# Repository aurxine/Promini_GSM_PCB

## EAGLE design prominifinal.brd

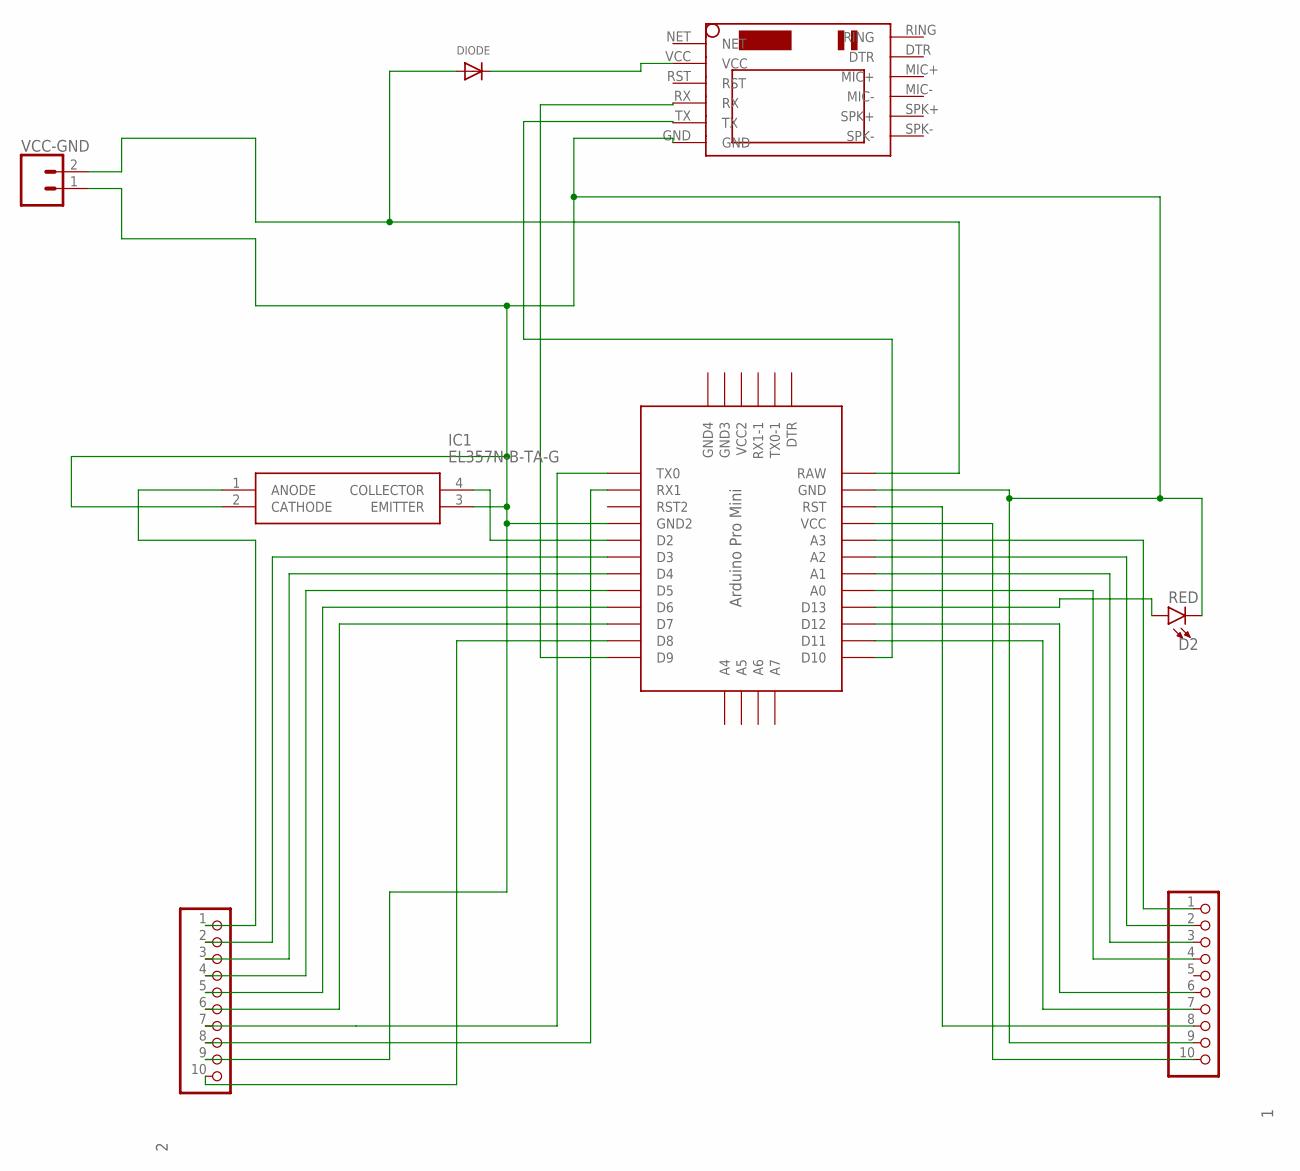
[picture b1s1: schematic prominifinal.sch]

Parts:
1, 2: PINHD-1X10; 1X10
D2: RED; LED-1206
DIODE: DIODESOD-323F; SOD-323F
IC1: EL357N-B-TA-G; SOP254P700X200-4N
PROMINI: PRO-MINI
U$1: SIM800LMODULE
VCC-GND: CONN_025MM; SCREWTERMINAL-5MM-2

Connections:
D2,D3,D4,D5-IO0,D6-IO2,D7-IO4,D8-IO5,D9-IO9,GND,VIN: 2.6, PROMINI.D7
unnamed: DIODE.A, PROMINI.RAW, VCC-GND.2
unnamed: 2.8, PROMINI.RX1
unnamed: DIODE.C, U$1.VCC
unnamed: 1.10, PROMINI.VCC
unnamed: IC1.4 (COLLECTOR), PROMINI.D2
unnamed: PROMINI.D9, U$1.RX
unnamed: D2.A, PROMINI.D13
unnamed: 2.1, IC1.1 (ANODE)
unnamed: 2.2, PROMINI.D3
unnamed: 2.3, PROMINI.D4
unnamed: 2.4, PROMINI.D5
unnamed: 2.5, PROMINI.D6
unnamed: 1.8, PROMINI.RST
unnamed: 2.7, PROMINI.TX0
unnamed: 2.10, PROMINI.D8
unnamed: 1.1, PROMINI.A3
unnamed: 1.2, PROMINI.A2
unnamed: 1.3, PROMINI.A1
unnamed: 1.4, PROMINI.A0
unnamed: 1.6, PROMINI.D12
unnamed: 1.7, PROMINI.D11
unnamed: PROMINI.D10, U$1.TX
unnamed: 1.9, 2.9, D2.C, IC1.2 (CATHODE), IC1.3 (EMITTER), PROMINI.GND, PROMINI.GND1 (GND2), U$1.GND, VCC-GND.1

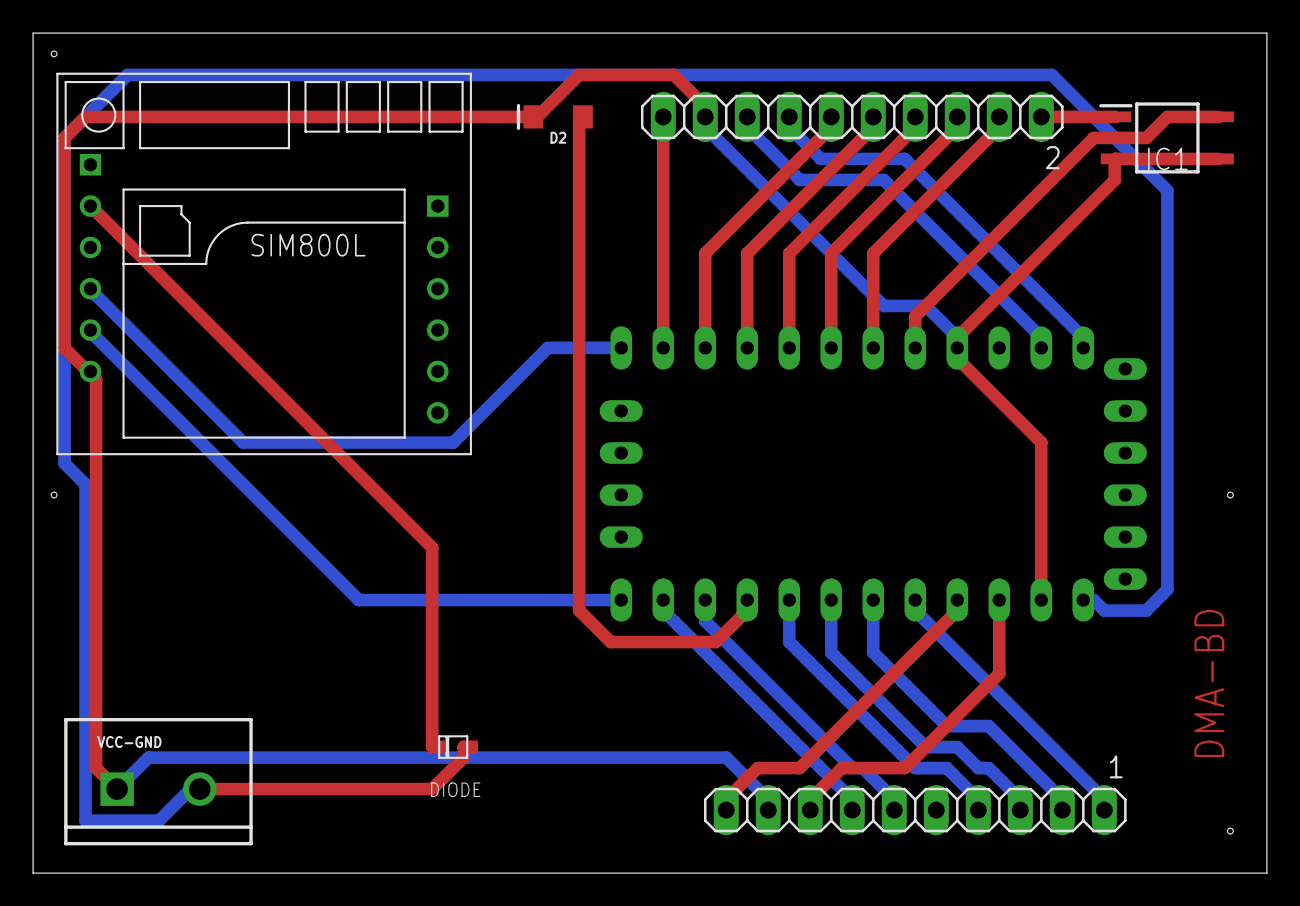
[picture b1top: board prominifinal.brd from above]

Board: 2 copper layers, 74.6 x 50.8 mm, 8 parts (0 on the bottom side), 24 nets.

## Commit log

2020-12-25 project file created
2020-12-25 schematic from esha added
2020-12-25 screw terminal set to 5mm
2020-12-25 tx rx and rst line added
2020-12-27 new files added
2020-12-27 added files
2020-12-27 final
2020-12-27 GND edit
2020-12-27 gerber file added
2020-12-28 silkscreen added

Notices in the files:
parts and their libraries:
SparkFun-LED: Licensing: Creative Commons ShareAlike 4.0 International - https://creativecommons.org/licenses/by-sa/4.0
